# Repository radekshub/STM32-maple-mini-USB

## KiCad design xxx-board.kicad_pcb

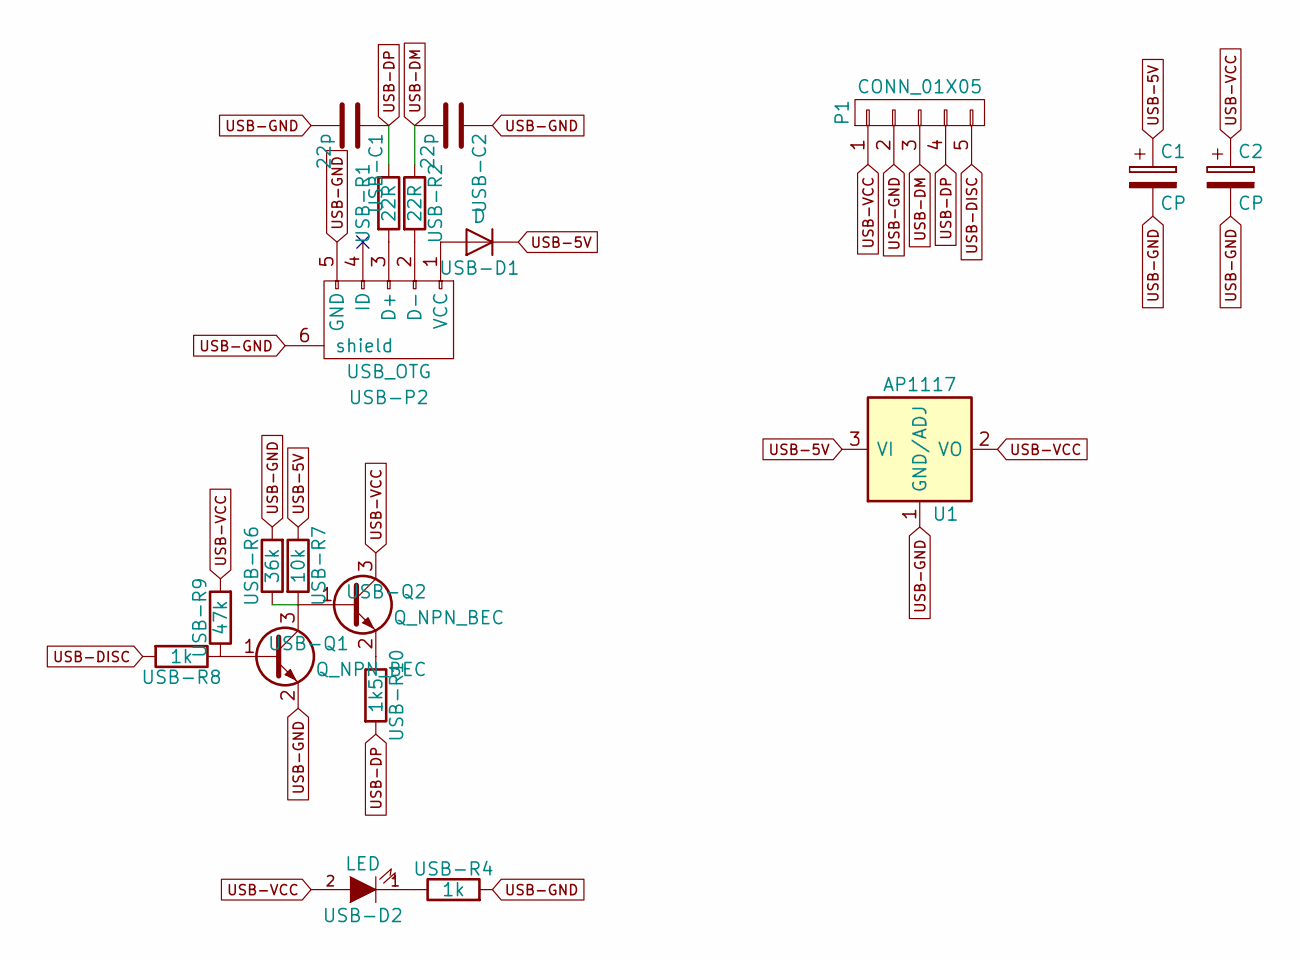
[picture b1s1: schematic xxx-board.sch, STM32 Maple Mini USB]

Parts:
C1, C2: CP; SMD-1210_Pol
P1: CONN_01X05; Pin_Header_Straight_1x05_Pitch2.54mm
U1: AP1117; SOT-223
USB-C1, USB-C2: 22p; C_0805
USB-D1: D; SMA_Standard
USB-D2: LED; LED_0805
USB-P2: USB_OTG; USB_Micro-B
USB-Q1, USB-Q2: Q_NPN_BEC; SOT-23
USB-R1, USB-R2: 22R; R_0805
USB-R4, USB-R8: 1k; R_0805
USB-R6: 36k; R_0805
USB-R7: 10k; R_0805
USB-R9: 47k; R_0805
USB-R10: 1k5; R_0805

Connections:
unnamed: USB-D1.2 (A), USB-P2.1 (VCC)
unnamed: USB-D2.1 (K), USB-R4.1
unnamed: USB-P2.2 (D-), USB-R2.2
unnamed: USB-P2.3 (D+), USB-R1.2
unnamed: USB-Q1.1 (B), USB-R8.1, USB-R9.1
unnamed: USB-Q1.3 (C), USB-Q2.1 (B), USB-R6.1, USB-R7.2
unnamed: USB-Q2.2 (E), USB-R10.1
USB-5V: C1.1, U1.3 (VI), USB-D1.1 (K), USB-R7.1
USB-DISC: P1.5, USB-R8.2
USB-DM: P1.3, USB-C2.2, USB-R2.1
USB-DP: P1.4, USB-C1.1, USB-R1.1, USB-R10.2
USB-GND: C1.2, C2.2, P1.2, U1.1 (GND/ADJ), USB-C1.2, USB-C2.1, USB-P2.5 (GND), USB-P2.6 (shield), USB-Q1.2 (E), USB-R4.2, USB-R6.2
USB-VCC: C2.1, P1.1, U1.2 (VO), U1.4 (VO), USB-D2.2 (A), USB-Q2.3 (C), USB-R9.2

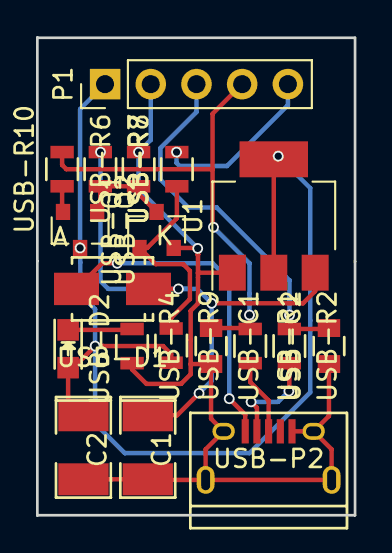
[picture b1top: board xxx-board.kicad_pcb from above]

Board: 2 copper layers, 17.7 x 26.5 mm, 19 parts (0 on the bottom side), 13 nets.

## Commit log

2019-01-19 Added files to repository.
